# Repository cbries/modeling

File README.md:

# Repository: modeling

This repository contains any source, configurations, etc.pp. to run my modelrailway.

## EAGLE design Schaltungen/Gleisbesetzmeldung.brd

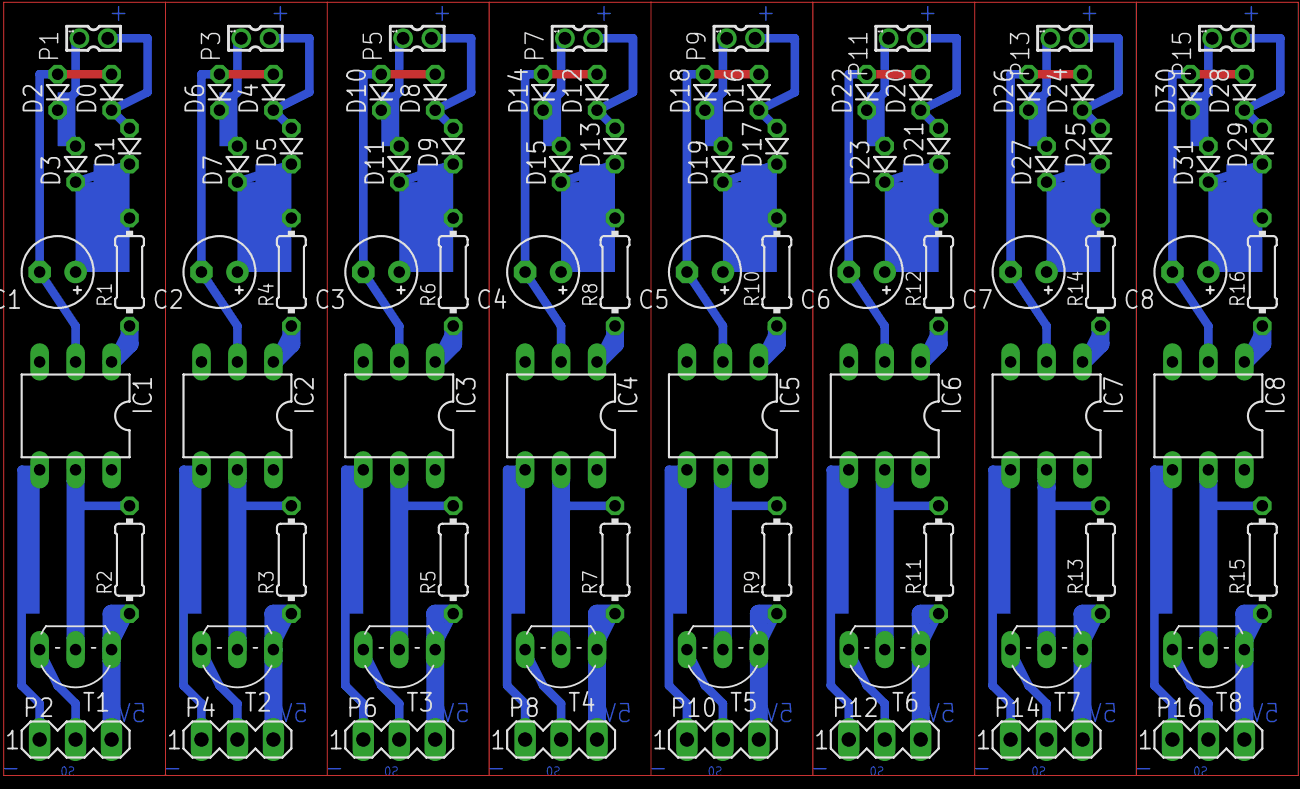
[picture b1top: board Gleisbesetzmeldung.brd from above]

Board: 2 copper layers, 88 parts (0 on the bottom side), 64 nets.

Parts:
C1, C2, C3, C4, C5, C6, C7, C8: 22uF, 35V; E2,5-5
D0, D1, D2, D3, D4, D5, D6, D7, D8, D9, D10, D11, D12, D13, D14, D15, D16, D17, D18, D19, D20, D21, D22, D23, D24, D25, D26, D27, D28, D29, D30, D31: D-2.5
IC1, IC2, IC3, IC4, IC5, IC6, IC7, IC8: CNY-17-2; DIL06
P1, P3, P5, P7, P9, P11, P13, P15: 87758-0216
P2, P4, P6, P8, P10, P12, P14, P16: MA03-1
R1, R2, R3, R4, R5, R6, R7, R8, R9, R10, R11, R12, R13, R14, R15, R16: 1k; 0204/7
T1, T2, T3, T4, T5, T6, T7, T8: TO92-CBE

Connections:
S$2: D0.C, D1.A
S$3: P2.3, R2.1, T1.C
S$4: IC1.5, IC1.6, R2.2, T1.B
S$5: D2.C, D3.A
S$6: C1.-, D0.A, D2.A, IC1.2
S$7: C1.+, D1.C, D3.C, R1.2
S$8: IC1.1, R1.1
S$11: IC1.4, P2.1, P2.2, T1.E
S$66: D4.C, D5.A
S$67: D6.C, D7.A
S$68: C2.-, D4.A, D6.A, IC2.2
S$69: C2.+, D5.C, D7.C, R4.2
S$70: IC2.1, R4.1
S$71: P4.3, R3.1, T2.C
S$72: IC2.5, IC2.6, R3.2, T2.B
S$73: IC2.4, P4.1, P4.2, T2.E
S$74: D8.C, D9.A
S$75: D10.C, D11.A
S$76: C3.-, D8.A, D10.A, IC3.2
S$77: C3.+, D9.C, D11.C, R6.2
S$78: IC3.1, R6.1
S$79: P6.3, R5.1, T3.C
S$80: IC3.5, IC3.6, R5.2, T3.B
S$81: IC3.4, P6.1, P6.2, T3.E
S$82: D12.C, D13.A
S$83: D14.C, D15.A
S$84: C4.-, D12.A, D14.A, IC4.2
S$85: C4.+, D13.C, D15.C, R8.2
S$86: IC4.1, R8.1
S$87: P8.3, R7.1, T4.C
S$88: IC4.5, IC4.6, R7.2, T4.B
S$89: IC4.4, P8.1, P8.2, T4.E
S$90: D16.C, D17.A
S$91: D18.C, D19.A
S$92: C5.-, D16.A, D18.A, IC5.2
S$93: C5.+, D17.C, D19.C, R10.2
S$94: IC5.1, R10.1
S$95: P10.3, R9.1, T5.C
S$96: IC5.5, IC5.6, R9.2, T5.B
S$97: IC5.4, P10.1, P10.2, T5.E
S$98: D20.C, D21.A
S$99: D22.C, D23.A
S$100: C6.-, D20.A, D22.A, IC6.2
S$101: C6.+, D21.C, D23.C, R12.2
S$102: IC6.1, R12.1
S$103: P12.3, R11.1, T6.C
S$104: IC6.5, IC6.6, R11.2, T6.B
S$105: IC6.4, P12.1, P12.2, T6.E
S$106: D24.C, D25.A
S$107: D26.C, D27.A
S$108: C7.-, D24.A, D26.A, IC7.2
S$109: C7.+, D25.C, D27.C, R14.2
S$110: IC7.1, R14.1
S$111: P14.3, R13.1, T7.C
S$112: IC7.5, IC7.6, R13.2, T7.B
S$113: IC7.4, P14.1, P14.2, T7.E
S$114: D28.C, D29.A
S$115: D30.C, D31.A
S$116: C8.-, D28.A, D30.A, IC8.2
S$117: C8.+, D29.C, D31.C, R16.2
S$118: IC8.1, R16.1
S$119: P16.3, R15.1, T8.C
S$120: IC8.5, IC8.6, R15.2, T8.B
S$121: IC8.4, P16.1, P16.2, T8.E

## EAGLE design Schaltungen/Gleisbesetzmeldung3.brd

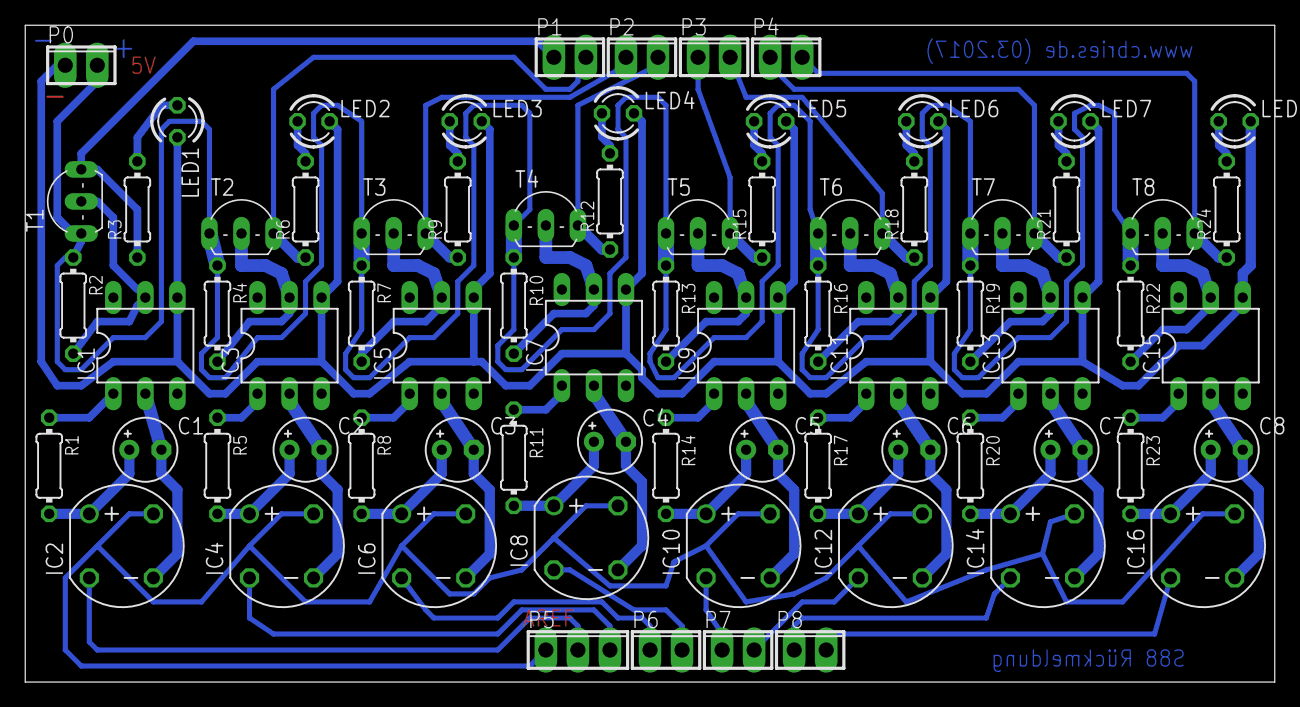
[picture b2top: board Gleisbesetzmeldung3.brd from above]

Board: 2 copper layers, 99.1 x 52.1 mm, 73 parts (0 on the bottom side), 26 nets.

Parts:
C1, C2, C3, C4, C5, C6, C7, C8: 22uF, 35V; E2,5-5
IC1, IC3, IC5, IC7, IC9, IC11, IC13, IC15: CNY-17-2; DIL06
IC2, IC4, IC6, IC8, IC10, IC12, IC14, IC16: S462; RB1A
LED1, LED2, LED3, LED4, LED5, LED6, LED7, LED8: LED3MM
P0, P1, P2, P3, P4, P6, P7, P8: 2POL254
P5: 3POL254
R1, R2, R4, R5, R7, R8, R10, R11, R13, R14, R16, R17, R19, R20, R22, R23: 1k; 0204/7
R3, R6, R9, R12, R15, R18, R21, R24: 220; 0204/7
T1, T2, T3, T4, T5, T6, T7, T8: TO92-CBE

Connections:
S$2: IC5.5, IC5.6, R7.2, T3.B
S$3: IC1.5, IC1.6, P0.2, R2.1, R2.2, R4.1, R7.1, R10.1, R13.1, R16.1, R19.1, R22.1, T1.B, T1.C, T2.C, T3.C, T4.C, T5.C, T6.C, T7.C, T8.C
S$5: IC1.4, IC3.4, IC5.4, IC7.4, IC9.4, IC11.4, IC13.4, IC15.4, LED1.A, LED1.K, LED2.A, LED2.K, LED3.A, LED3.K, LED4.A, LED4.K, LED5.A, LED5.K, LED6.A, LED6.K, LED7.A, LED7.K, LED8.A, LED8.K, P0.1, P1.1, P1.2, P2.1, P2.2, P3.1, P3.2, P4.1, P4.2, R3.1, R3.2, R6.1, R6.2, R9.1, R9.2, R12.1, R12.2, R15.1, R15.2, R18.1, R18.2, R21.1, R21.2, R24.1, R24.2, T1.E, T2.E, T3.E, T4.E, T5.E, T6.E, T7.E, T8.E
S$6: C2.+, IC4.+, R5.2
S$7: C1.+, IC2.+, R1.2
S$8: IC1.1, R1.1
S$11: IC3.1, R5.1
S$124: IC3.5, IC3.6, R4.2, T2.B
S$127: C3.+, IC6.+, R8.2
S$128: IC5.1, R8.1
S$133: C4.+, IC8.+, R11.2
S$134: IC7.1, R11.1
S$136: IC7.5, IC7.6, R10.2, T4.B
S$139: C5.+, IC10.+, R14.2
S$140: IC9.1, R14.1
S$142: IC9.5, IC9.6, R13.2, T5.B
S$145: C6.+, IC12.+, R17.2
S$146: IC11.1, R17.1
S$148: IC11.5, IC11.6, R16.2, T6.B
S$151: C7.+, IC14.+, R20.2
S$152: IC13.1, R20.1
S$154: IC13.5, IC13.6, R19.2, T7.B
S$157: C8.+, IC16.+, R23.2
S$158: IC15.1, R23.1
S$160: IC15.5, IC15.6, R22.2, T8.B
S$162: C1.-, C2.-, C3.-, C4.-, C5.-, C6.-, C7.-, C8.-, IC1.2, IC2.-, IC2.AC1, IC2.AC2, IC3.2, IC4.-, IC4.AC1, IC4.AC2, IC5.2, IC6.-, IC6.AC1, IC6.AC2, IC7.2, IC8.-, IC8.AC1, IC8.AC2, IC9.2, IC10.-, IC10.AC1, IC10.AC2, IC11.2, IC12.-, IC12.AC1, IC12.AC2, IC13.2, IC14.-, IC14.AC1, IC14.AC2, IC15.2, IC16.-, IC16.AC1, IC16.AC2, P5.1, P5.2, P5.3, P6.1, P6.2, P7.1, P7.2, P8.1, P8.2

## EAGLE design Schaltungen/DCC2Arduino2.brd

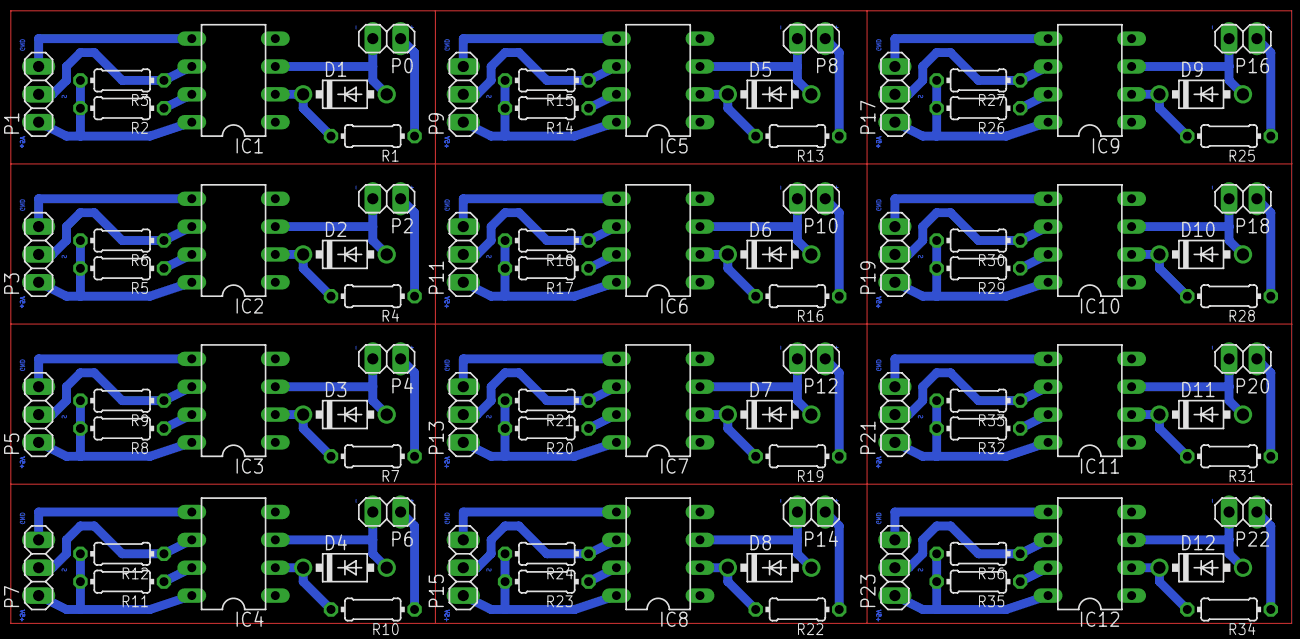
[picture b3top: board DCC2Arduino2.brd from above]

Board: 2 copper layers, 84 parts (0 on the bottom side), 84 nets.

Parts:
D1, D2, D3, D4, D5, D6, D7, D8, D9, D10, D11, D12: 1N4148; DO41-7
IC1, IC2, IC3, IC4, IC5, IC6, IC7, IC8, IC9, IC10, IC11, IC12: 6N137; DIL08
P0, P2, P4, P6, P8, P10, P12, P14, P16, P18, P20, P22: 1X02
P1, P3, P5, P7, P9, P11, P13, P15, P17, P19, P21, P23: 1X03
R1, R4, R7, R10, R13, R16, R19, R22, R25, R28, R31, R34: 1k; 0204/7
R2, R3, R5, R6, R8, R9, R11, R12, R14, R15, R17, R18, R20, R21, R23, R24, R26, R27, R29, R30, R32, R33, R35, R36: 10k; 0204/7

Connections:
S$2: P0.1, R1.1
S$3: IC1.5, P1.3
S$4: D1.A, IC1.3, P0.2
S$5: D1.C, IC1.2, R1.2
S$6: IC1.8, P1.1, R3.2
S$7: IC1.7, R2.1
S$8: P2.1, R4.1
S$9: IC1.6, P1.2, R3.1
S$10: D2.A, IC2.3, P2.2
S$11: D2.C, IC2.2, R4.2
S$12: IC2.8, P3.1, R6.2
S$13: IC2.7, R5.1
S$14: IC2.6, P3.2, R6.1
S$15: IC2.5, P3.3
S$16: P4.1, R7.1
S$17: D3.A, IC3.3, P4.2
S$18: D3.C, IC3.2, R7.2
S$19: IC3.8, P5.1, R9.2
S$20: IC3.7, R8.1
S$21: IC3.6, P5.2, R9.1
S$22: IC3.5, P5.3
S$23: P6.1, R10.1
S$24: D4.A, IC4.3, P6.2
S$25: D4.C, IC4.2, R10.2
S$26: IC4.8, P7.1, R12.2
S$27: IC4.7, R11.1
S$28: IC4.6, P7.2, R12.1
S$29: IC4.5, P7.3
S$86: P8.1, R13.1
S$87: D5.A, IC5.3, P8.2
S$88: D5.C, IC5.2, R13.2
S$89: IC5.8, P9.1, R15.2
S$90: IC5.7, R14.1
S$91: IC5.6, P9.2, R15.1
S$92: IC5.5, P9.3
S$93: P10.1, R16.1
S$94: D6.A, IC6.3, P10.2
S$95: D6.C, IC6.2, R16.2
S$96: IC6.8, P11.1, R18.2
S$97: IC6.7, R17.1
S$98: IC6.6, P11.2, R18.1
S$99: IC6.5, P11.3
S$100: P12.1, R19.1
S$101: D7.A, IC7.3, P12.2
S$102: D7.C, IC7.2, R19.2
S$103: IC7.8, P13.1, R21.2
S$104: IC7.7, R20.1
S$105: IC7.6, P13.2, R21.1
S$106: IC7.5, P13.3
S$107: P14.1, R22.1
S$108: D8.A, IC8.3, P14.2
S$109: D8.C, IC8.2, R22.2
S$110: IC8.8, P15.1, R24.2
S$111: IC8.7, R23.1
S$112: IC8.6, P15.2, R24.1
S$113: IC8.5, P15.3
S$114: P16.1, R25.1
S$115: D9.A, IC9.3, P16.2
S$116: D9.C, IC9.2, R25.2
S$117: IC9.8, P17.1, R27.2
S$118: IC9.7, R26.1
S$119: IC9.6, P17.2, R27.1
S$120: IC9.5, P17.3
S$121: P18.1, R28.1
S$122: D10.A, IC10.3, P18.2
S$123: D10.C, IC10.2, R28.2
S$124: IC10.8, P19.1, R30.2
S$125: IC10.7, R29.1
S$126: IC10.6, P19.2, R30.1
S$127: IC10.5, P19.3
S$128: P20.1, R31.1
S$129: D11.A, IC11.3, P20.2
S$130: D11.C, IC11.2, R31.2
S$131: IC11.8, P21.1, R33.2
S$132: IC11.7, R32.1
S$133: IC11.6, P21.2, R33.1
S$134: IC11.5, P21.3
S$135: P22.1, R34.1
S$136: D12.A, IC12.3, P22.2
S$137: D12.C, IC12.2, R34.2
S$138: IC12.8, P23.1, R36.2
S$139: IC12.7, R35.1
S$140: IC12.6, P23.2, R36.1
S$141: IC12.5, P23.3

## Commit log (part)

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2017-03-14 howtos
2017-03-20 pdf of plan
2017-03-25 longrunning servo test
2017-03-25 faster test. i.e. 44 runs/min, 2640 runs/hour
2017-03-26 second longterm test
2017-03-26 strange behaviour
2017-03-26 rollback
2017-03-26 Fritzing "Gleisbesetzmeldung", Export as Image
2017-03-26 mit dioden
2017-03-26 improved
2017-03-26 Eagle Schematic
2017-03-27 prototype
2017-03-27 dcc to arduino
2017-03-29 gerber files
2017-04-09 rahmenbau
2017-04-09 rahmen
2017-04-10 rahmenplanung
2017-06-20 Weichensteuerung
2017-06-25 s88 update
2017-06-26 label for the s88-rj45 bridge
2017-06-26 update documentation
2017-06-26 Planung
2017-06-28 exports
2017-07-02 s88 update for servos
2017-07-05 Lichtschranke
2017-07-07 Schaltungsbug
2017-07-10 start of commands
2017-07-11 command handling stuff
2017-07-11 parse replies
2017-07-11 preparation for track plans
2017-07-11 communication to the ecos2
2017-07-11 git chaos
2017-07-11 support events
2017-07-11 documentation, speed control & fnc tests
2017-07-11 general checkin
2017-07-11 blah
2017-07-12 communicator, data handling, and add theming icon
2017-07-12 table generator
2017-07-12 tree view provides status
2017-07-12 blubb
2017-07-13 web ui, js callback, execute js from csharp, etc.
2017-07-13 property changed notifier
2017-07-13 some improvements
2017-07-13 prepare serialization/deserialization
2017-07-13 storing
2017-07-14 load objects; cef part of test ui
2017-07-14 general update
2017-07-14 first editor version
2017-07-14 improved designer, new approach
2017-07-15 drag&drop works, images aligned correctly, few improvements
2017-07-15 serialization/deserialization
2017-07-15 csv remove, now json, load of track plan, store of track plan, rotation applied during load
2017-07-16 refactoring
2017-07-16 first track mapping, signals are perfectly shown on the trackplan :-D
2017-07-16 toggle edit mode
2017-07-16 fix: rotation
2017-07-16 ignore one symbol
2017-07-16 weave by config file instead of manually added code
2017-07-16 fix nullptr
2017-07-16 few more planned WeaveItem types
2017-07-17 selection with categories started
2017-07-18 ui improvements
2017-07-18 theming
2017-07-18 track objects have id instead of symbol names
2017-07-18 change track symbols on events based on theme information
2017-07-18 click feedback, switches works (!!)
2017-07-19 vs'17
2017-07-19 mdi lib for ui
2017-07-20 mdi stuff
2017-07-27 after vacation
2017-07-27 build fix
2017-07-27 cfg save/restore, logging, connect to station fixed
2017-07-28 rich changes
2017-07-28 ui update works again
2017-07-28 loc control is back, sync of current state with tree view fixed
2017-07-28 treeview update
2017-07-29 rot fixed, plan fixed
2017-07-29 fix: edit mode
2017-07-29 toggle edit mode from c#, fix table size to be fixed
2017-07-29 cleanup
2017-07-29 performance (!!)
2017-07-30 add track "views", harddisk cleanup
2017-07-30 window naming
2017-07-30 provide "go/stop" command
2017-07-30 provide go/stop status in tree view
2017-07-30 performance
2017-07-30 provide correct locomotive stop
2017-07-30 promote current locomotive state correctly
2017-07-30 object sync
2017-07-30 improvements
2017-07-30 fix: current locomotive state
2017-07-30 use radio boxes instead of keyboard controls to distiguish edit modes
2017-07-30 performance measurement for UI updates
2017-07-30 provide coord info in object assignment
2017-07-30 prepare save of weaving
2017-07-31 save assignments
2017-07-31 dry mode and serialization
2017-07-31 coord fix
2017-07-31 add prism telnet lib to solution instead of nuget pkg
2017-07-31 allow s88 pin setup
2017-07-31 fix: dryrun cmd state when connected
2017-07-31 documentation
2017-08-01 sync s88 objects, allow edit mode only in dry or connected mode, mouseover effects within the designer, cleanup
2017-08-01 start of analyzing routes
2017-08-13 fix: project creation
2017-08-13 fix: move of track items
2017-08-14 fix: query of neighbours
2017-08-14 add todo description
2017-08-15 fix: neighbour finding
2017-08-15 does not work correctly (!!)
2017-08-16 first depth-first search approach
2017-08-16 promising
2017-08-18 query routes work
2017-08-18 recognize directions
2017-08-18 try to handle connectors
2017-08-19 connectors are work
2017-08-19 serialize/deserialze waypoints
2017-08-19 fix: project reopen fix: isdirty flag fix: start block not added to route
2017-08-19 start/stop hightlight, rotate alignment fixed
2017-08-20 update test project
2017-08-20 fix: query route correctly when several switches are passed
2017-08-20 provide recent project open
2017-08-20 start of multiple views
2017-08-20 provide edit of track entity's name and desciption
2017-08-20 provide individual item names with count during drop
2017-08-20 provide names of block routes instead of coord in explorer
2017-08-20 provide about dlg
2017-08-20 ui stuff
2017-08-22 provide ids for switches, blocks, signals, and sensors
2017-08-24 labeling
2017-08-24 assign locomotives to blocks, provide correct labels
2017-08-25 disable auto tab select
2017-08-25 ui and icons
2017-08-25 provide base infrastructure for autoplay
2017-08-25 first step of configuring events
2017-08-26 anaöyzing block routes, i.e. routes which cross any other routes
2017-08-27 set route "active" visualization
2017-08-27 current switch state during route preview
2017-08-28 query correct turn state of switches/branches
2017-08-28 test projectes
2017-08-28 remove ugly projects
2017-08-29 fix : thread cleanup
2017-08-29 autoplay
2017-08-29 still something to do
2017-08-30 s88 feedback and block action
2017-08-30 inverting ecos command
2017-08-30 start test with live system
2017-08-30 testing with live system
2017-08-30 test with live system
2017-08-30 missing merge
2017-08-30 minimize output
2017-08-30 fix null ptr exception
2017-08-30 cleanup; fix null ptr
2017-08-30 testing
2017-08-30 reset previous route after run
2017-08-30 update blocks
2017-08-30 FULL TEST :-D
2017-08-30 it works !!!
2017-08-31 add license text
2017-08-31 avoid second run of locomotive after stop
2017-08-31 provide individual loc block speed when block entered
2017-09-01 properitary svg files removed; add svg generator, provide photoshop track icon tpl file; start of setup
2017-09-01 more icons
2017-09-01 additional theme track files
2017-09-01 additional track icons
2017-09-01 additional theme files
2017-09-01 additional theme icons
2017-09-01 theme files
2017-09-01 add additional theme files
2017-09-02 fix: remove "xlink"
2017-09-02 fix: routed s88 visualization; provide ctx menu to stop locs, provide ctx menu for route visualization; reset any switch during system start
2017-09-02 provide: send loc to target block
2017-09-02 update assembly infos
2017-09-02 fix: is dirty flag; remove environment variable
2017-09-02 fix: space issues with path during cef load
2017-09-02 app icon update
2017-09-02 update setup
2017-09-02 provide example projects; improve setup; uninstall before install within setup
2017-09-02 example project updates
2017-09-02 thread issue
2017-09-02 "RailwayEssential" moved to "https://github.com/cbries/railwayessential"
2017-12-05 servo configs
2017-12-10 shbf#2 switch added
2017-12-18 plan of rocrail
2017-12-20 kreuzende Blöcke
2017-12-20 running system
2017-12-23 plan update
2017-12-24 block gruppen
2017-12-24 track route updates
2017-12-27 servos separated
2018-01-02 locomotive images
2018-01-02 fahrstrassen update
2018-01-03 lokomotive fotos
2018-01-09 start of panorama
2018-01-14 background
2018-01-22 dcc control for segmentdrehscheibe
2018-01-23 segmentdrehscheibe software for arduino uno
2018-01-24 dcc uno segmentdrehscheibe
2018-01-25 values
2018-01-28 additional s88
2018-01-28 current state
2018-01-28 segmentdrehscheibe
2018-02-02 Bruecke
2018-02-07 some switches, some new locomotives, general updates
2018-02-23 druckvorlagen
2018-03-11 Bahnhofsbeleuchtung
2018-03-11 remove serial
2018-04-24 some locs removed
2018-05-01 add Andreaskreuz ino
2018-05-10 led stripe with websocket
2018-05-10 store in eeprom after disconnect
2018-06-03 few updates
2018-06-03 add tool for daylight control
2018-06-03 plan update and set daylight tooling
2018-06-04 action for one block
2018-06-04 lok images
2018-06-05 remove unused files
2018-06-05 new order
2018-06-05 rename
2018-06-05 umstrukturieren
2018-06-05 allow modification of fade steps and fade timeouts
2018-06-05 lok image updates
2018-06-05 add lok images for esu ecos
2018-06-05 some fixes
2018-06-05 restore stuff
2018-06-05 additional routes
2018-06-05 Sonnenauf- und -untergang
2018-06-06 better error handling, changed deployment directory
2018-06-06 Revert "Merge branch 'master' of https://github.com/cbries/modeling"
    This reverts commit d0796a483249cf713245db42b9a103b4c27e9a8d, reversing
    changes made to 7818e76a419714dd73424f3a01e887934244cc82.
2018-06-06 Revert "Revert "Merge branch 'master' of https://github.com/cbries/modeling""
    This reverts commit da33f7efdd7dfa158713663560818b962e3c9610.
2018-06-08 update locomotive settings
2018-06-08 recent state
2018-06-13 general commit
2018-06-18 try to use .netcore
2018-06-20 add bash script for changing day light over websocket
2018-06-24 IoT Steckdosen
2018-07-02 changed wlan settings for led stripe
2018-07-03 wlan updates
2018-09-09 Strassenbahn PingPong created
2018-10-30 sensors works, i.e. gyroscope, hall sensor, temperature, and humidity
2018-10-31 prepare some data
2018-11-01 running messwagen
2018-11-18 allow to change steckdose by rocrail
2018-11-18 deploy after build
2018-11-18 add steckdosen buttons
2018-11-18 tools for generating webcam shot as png
2018-11-18 add webcam support; fix wlan
2018-11-21 changed ip
2019-06-15 larger clean up
2021-01-29 Bump log4net from 2.0.3 to 2.0.10 in /Rocrail/RocrailTools/RocrailTools
    Bumps [log4net](https://github.com/apache/logging-log4net) from 2.0.3 to 2.0.10.
    - [Release notes](https://github.com/apache/logging-log4net/releases)
    - [Changelog](https://github.com/apache/logging-log4net/blob/master/ReleaseInstructions.txt)
    - [Commits](https://github.com/apache/logging-log4net/commits/rel/2.0.10)
2022-06-22 Bump Newtonsoft.Json in /Rocrail/RocrailTools/SetDayLightDotNet
    Bumps [Newtonsoft.Json](https://github.com/JamesNK/Newtonsoft.Json) from 11.0.2 to 13.0.1.
    - [Release notes](https://github.com/JamesNK/Newtonsoft.Json/releases)
    - [Commits](https://github.com/JamesNK/Newtonsoft.Json/compare/11.0.2...13.0.1)
    ---
    updated-dependencies:
    - dependency-name: Newtonsoft.Json
2022-06-22 Bump Newtonsoft.Json in /Rocrail/RocrailTools/RocrailTools
    Bumps [Newtonsoft.Json](https://github.com/JamesNK/Newtonsoft.Json) from 11.0.2 to 13.0.1.
    - [Release notes](https://github.com/JamesNK/Newtonsoft.Json/releases)
    - [Commits](https://github.com/JamesNK/Newtonsoft.Json/compare/11.0.2...13.0.1)
    ---
    updated-dependencies:
    - dependency-name: Newtonsoft.Json
2022-06-22 Bump Newtonsoft.Json in /Rocrail/RocrailTools/SetIoTSteckdose
    Bumps [Newtonsoft.Json](https://github.com/JamesNK/Newtonsoft.Json) from 11.0.2 to 13.0.1.
    - [Release notes](https://github.com/JamesNK/Newtonsoft.Json/releases)
    - [Commits](https://github.com/JamesNK/Newtonsoft.Json/compare/11.0.2...13.0.1)
    ---
    updated-dependencies:
    - dependency-name: Newtonsoft.Json
2022-12-08 Bump Newtonsoft.Json in /Rocrail/RocrailTools/SetDayLightDotNet
    Bumps [Newtonsoft.Json](https://github.com/JamesNK/Newtonsoft.Json) from 11.0.2 to 13.0.2.
    - [Release notes](https://github.com/JamesNK/Newtonsoft.Json/releases)
    - [Commits](https://github.com/JamesNK/Newtonsoft.Json/compare/11.0.2...13.0.2)
    ---
    updated-dependencies:
    - dependency-name: Newtonsoft.Json
2022-12-08 Bump Newtonsoft.Json in /Rocrail/RocrailTools/SetIoTSteckdose
    Bumps [Newtonsoft.Json](https://github.com/JamesNK/Newtonsoft.Json) from 11.0.2 to 13.0.2.
    - [Release notes](https://github.com/JamesNK/Newtonsoft.Json/releases)
    - [Commits](https://github.com/JamesNK/Newtonsoft.Json/compare/11.0.2...13.0.2)
    ---
    updated-dependencies:
    - dependency-name: Newtonsoft.Json
2023-06-02 update Switches to mqtt
2023-06-03 add mqtt to rgba stripe
2023-06-04 change mqtt id
2023-06-22 add missing files
2023-06-22 Brand new plan based on Rocrail
2023-06-22 keep backups
